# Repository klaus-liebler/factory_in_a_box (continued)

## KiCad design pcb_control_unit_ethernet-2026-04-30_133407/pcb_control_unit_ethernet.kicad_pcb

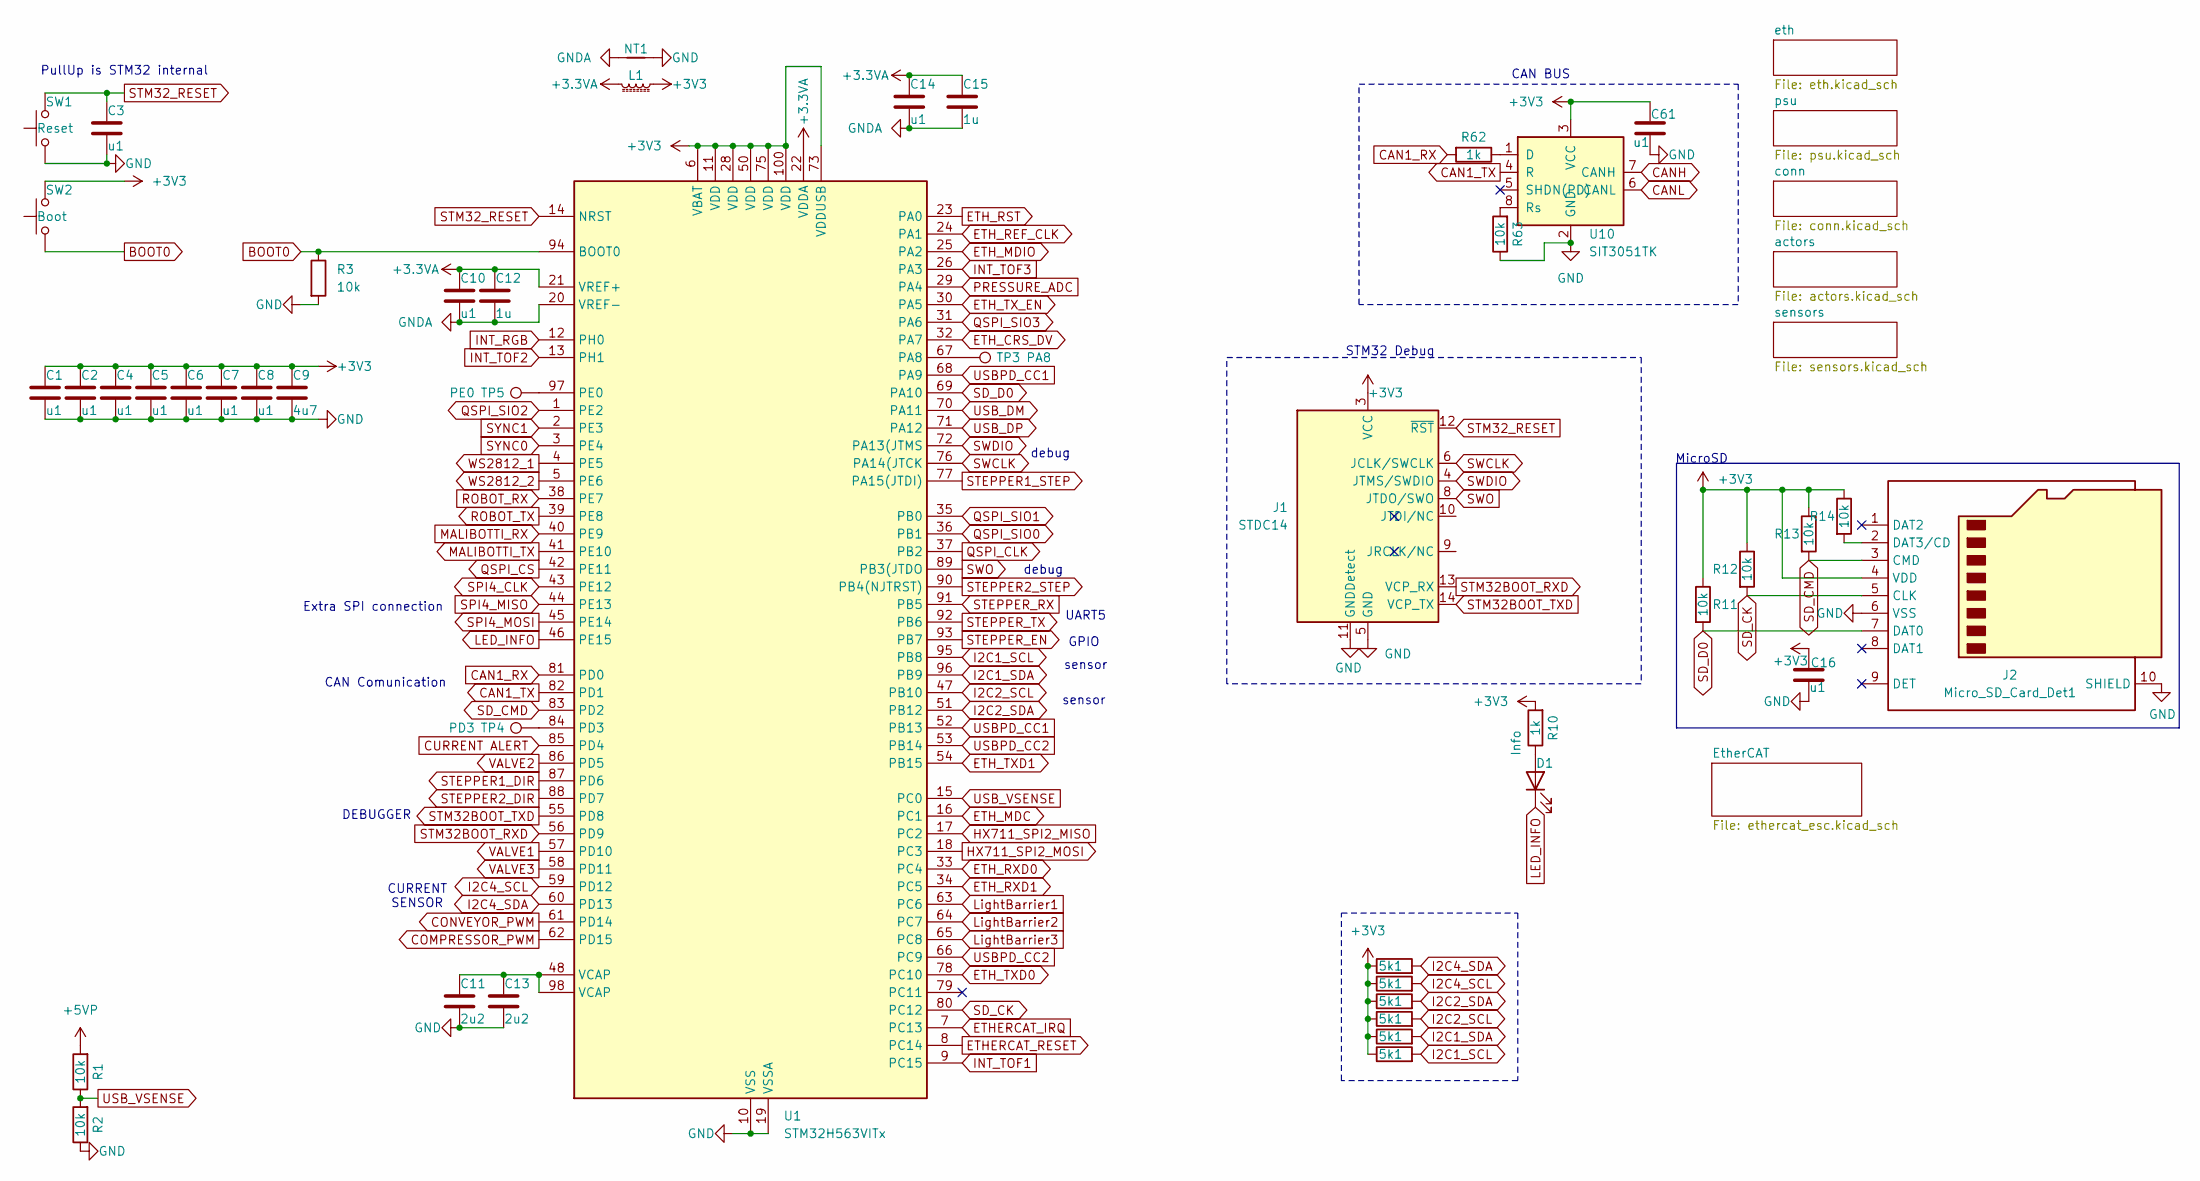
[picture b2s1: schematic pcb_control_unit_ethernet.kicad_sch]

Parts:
C1, C2, C3, C4, C5, C6, C7, C8, C10, C14: u1; C_0402_1005Metric
C9: 4u7; C_0402_1005Metric
C11, C13: 2u2; C_0402_1005Metric
C12, C15: 1u; C_0402_1005Metric
C16, C61: u1; C_0402_1005Metric; MPN GRM033R61A104KE15D
D1: Info; LED_1206_3216Metric_ReverseMount; MPN LTST-C230KRKT
J1: STDC14; IDC-Header_2x07_P1.27mm_Vertical_SMD
J2: Micro_SD_Card_Det1; microSD push; MPN TF PUSH
L1: 220R@100M; L_0603_1608Metric
NT1: NetTie_2; NetTie-2_SMD_Pad0.5mm
R1, R2, R11, R12, R13, R14, R63: 10k; R_0402_1005Metric; MPN 0201WMF1002TEE
R3: 10k; R_0402_1005Metric
R4, R5, R6, R7, R8, R9: 5k1; R_0402_1005Metric
R10, R62: 1k; R_0402_1005Metric; MPN 0402WGF1001TCE
SW1: Reset; SW_SPST_TL3342_smaller
SW2: Boot; SW_SPST_TL3342_smaller
TP3: PA8; TestPoint_THTPad_D1.0mm_Drill0.5mm
TP4: PD3; TestPoint_THTPad_D1.0mm_Drill0.5mm
TP5: PE0; TestPoint_THTPad_D1.0mm_Drill0.5mm
U1: STM32H563VITx; LQFP-100_14x14mm_P0.5mm
U10: SIT3051TK; DFN-8-1EP_3x3mm_P0.65mm_EP1.55x2.4mm

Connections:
+3.3VA: C10.1, C12.1, C14.1, C15.1, L1.2, U1.21 (VREF+), U1.22 (VDDA)
+3V3: C1.1, C2.1, C4.1, C5.1, C6.1, C7.1, C8.1, C9.1, C16.2, C61.1, J1.3 (VCC), J2.4 (VDD), L1.1, R4.1, R5.1, R6.1, R7.1, R8.1, R9.1, R10.2, R11.1, R12.1, R13.1, R14.1, SW2.2, U1.6 (VBAT), U1.11 (VDD), U1.28 (VDD), U1.50 (VDD), U1.73 (VDDUSB), U1.75 (VDD), U1.100 (VDD), U10.3 (VCC); also elsewhere on the board
+5VP: R1.2; also elsewhere on the board
BOOT0: R3.1, SW2.1, U1.94 (BOOT0)
CAN1_RX: R62.2, U1.81 (PD0)
CAN1_TX: U1.82 (PD1), U10.4 (R)
CANH: U10.7 (CANH); also elsewhere on the board
CANL: U10.6 (CANL); also elsewhere on the board
COMPRESSOR_PWM: U1.62 (PD15); also elsewhere on the board
CONVEYOR_PWM: U1.61 (PD14); also elsewhere on the board
CURRENT ALERT: U1.85 (PD4); also elsewhere on the board
ETHERCAT_IRQ: U1.7 (PC13); also elsewhere on the board
ETHERCAT_RESET: U1.8 (PC14); also elsewhere on the board
ETH_CRS_DV: U1.32 (PA7); also elsewhere on the board
ETH_MDC: U1.16 (PC1); also elsewhere on the board
ETH_MDIO: U1.25 (PA2); also elsewhere on the board
ETH_REF_CLK: U1.24 (PA1); also elsewhere on the board
ETH_RST: U1.23 (PA0); also elsewhere on the board
ETH_RXD0: U1.33 (PC4); also elsewhere on the board
ETH_RXD1: U1.34 (PC5); also elsewhere on the board
ETH_TXD0: U1.78 (PC10); also elsewhere on the board
ETH_TXD1: U1.54 (PB15); also elsewhere on the board
ETH_TX_EN: U1.30 (PA5); also elsewhere on the board
GND: C1.2, C2.2, C3.2, C4.2, C5.2, C6.2, C7.2, C8.2, C9.2, C11.2, C13.2, C16.1, C61.2, J1.5 (GND), J1.7 (GND), J1.11 (GNDDetect), J2.6 (VSS), J2.10 (SHIELD), NT1.2, R2.1, R3.2, R63.1, SW1.1, U1.10 (VSS), U1.19 (VSSA), U1.27 (VSS), U1.49 (VSS), U1.74 (VSS), U1.99 (VSS), U10.2 (GND), U10.9 (PAD); also elsewhere on the board
GNDA: C10.2, C12.2, C14.2, C15.2, NT1.1, U1.20 (VREF-)
HX711_SPI2_MISO: U1.17 (PC2); also elsewhere on the board
HX711_SPI2_MOSI: U1.18 (PC3); also elsewhere on the board
I2C1_SCL: R9.2, U1.95 (PB8); also elsewhere on the board
I2C1_SDA: R8.2, U1.96 (PB9); also elsewhere on the board
I2C2_SCL: R7.2, U1.47 (PB10); also elsewhere on the board
I2C2_SDA: R6.2, U1.51 (PB12); also elsewhere on the board
I2C4_SCL: R5.2, U1.59 (PD12); also elsewhere on the board
I2C4_SDA: R4.2, U1.60 (PD13); also elsewhere on the board
INT_RGB: U1.12 (PH0); also elsewhere on the board
INT_TOF1: U1.9 (PC15); also elsewhere on the board
INT_TOF2: U1.13 (PH1); also elsewhere on the board
INT_TOF3: U1.26 (PA3); also elsewhere on the board
LED_INFO: D1.1 (K), U1.46 (PE15)
LightBarrier1: U1.63 (PC6); also elsewhere on the board
LightBarrier2: U1.64 (PC7); also elsewhere on the board
LightBarrier3: U1.65 (PC8); also elsewhere on the board
MALIBOTTI_RX: U1.40 (PE9); also elsewhere on the board
MALIBOTTI_TX: U1.41 (PE10); also elsewhere on the board
unnamed: C11.1, C13.1, U1.48 (VCAP), U1.98 (VCAP)
unnamed: D1.2 (A), R10.1
unnamed: J2.2 (DAT3/CD), R14.2
unnamed: TP3.1 (1_1), U1.67 (PA8)
unnamed: TP4.1 (1_1), U1.84 (PD3)
unnamed: TP5.1 (1_1), U1.97 (PE0)
unnamed: R62.1, U10.1 (D)
unnamed: R63.2, U10.8 (Rs)
PRESSURE_ADC: U1.29 (PA4); also elsewhere on the board
QSPI_CLK: U1.37 (PB2); also elsewhere on the board
QSPI_CS: U1.42 (PE11); also elsewhere on the board
QSPI_SIO0: U1.36 (PB1); also elsewhere on the board
QSPI_SIO1: U1.35 (PB0); also elsewhere on the board
QSPI_SIO2: U1.1 (PE2); also elsewhere on the board
QSPI_SIO3: U1.31 (PA6); also elsewhere on the board
ROBOT_RX: U1.38 (PE7); also elsewhere on the board
ROBOT_TX: U1.39 (PE8); also elsewhere on the board
SD_CK: J2.5 (CLK), R12.2, U1.80 (PC12)
SD_CMD: J2.3 (CMD), R13.2, U1.83 (PD2)
SD_D0: J2.7 (DAT0), R11.2, U1.69 (PA10)
SPI4_CLK: U1.43 (PE12); also elsewhere on the board
SPI4_MISO: U1.44 (PE13); also elsewhere on the board
SPI4_MOSI: U1.45 (PE14); also elsewhere on the board
STEPPER1_DIR: U1.87 (PD6); also elsewhere on the board
STEPPER1_STEP: U1.77 (PA15(JTDI)); also elsewhere on the board
STEPPER2_DIR: U1.88 (PD7); also elsewhere on the board
STEPPER2_STEP: U1.90 (PB4(NJTRST)); also elsewhere on the board
STEPPER_EN: U1.93 (PB7); also elsewhere on the board
STEPPER_RX: U1.91 (PB5); also elsewhere on the board
STEPPER_TX: U1.92 (PB6); also elsewhere on the board
STM32BOOT_RXD: J1.13 (VCP_RX), U1.56 (PD9)
STM32BOOT_TXD: J1.14 (VCP_TX), U1.55 (PD8)
STM32_RESET: C3.1, J1.12 (~RST), SW1.2, U1.14 (NRST)
SWCLK: J1.6 (JCLK/SWCLK), U1.76 (PA14(JTCK)
SWDIO: J1.4 (JTMS/SWDIO), U1.72 (PA13(JTMS)
SWO: J1.8 (JTDO/SWO), U1.89 (PB3(JTDO)
SYNC0: U1.3 (PE4); also elsewhere on the board
SYNC1: U1.2 (PE3); also elsewhere on the board
USBPD_CC1: U1.52 (PB13), U1.68 (PA9); also elsewhere on the board
USBPD_CC2: U1.53 (PB14), U1.66 (PC9); also elsewhere on the board
USB_DM: U1.70 (PA11); also elsewhere on the board
USB_DP: U1.71 (PA12); also elsewhere on the board
USB_VSENSE: R1.1, R2.2, U1.15 (PC0)
VALVE1: U1.57 (PD10); also elsewhere on the board
VALVE2: U1.86 (PD5); also elsewhere on the board
VALVE3: U1.58 (PD11); also elsewhere on the board
WS2812_1: U1.4 (PE5); also elsewhere on the board
WS2812_2: U1.5 (PE6); also elsewhere on the board

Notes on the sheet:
CAN Comunication
debug
MicroSD
UART5
CAN BUS
DEBUGGER
sensor
STM32 Debug
CURRENT SENSOR
PullUp is STM32 internal
Extra SPI connection
GPIO

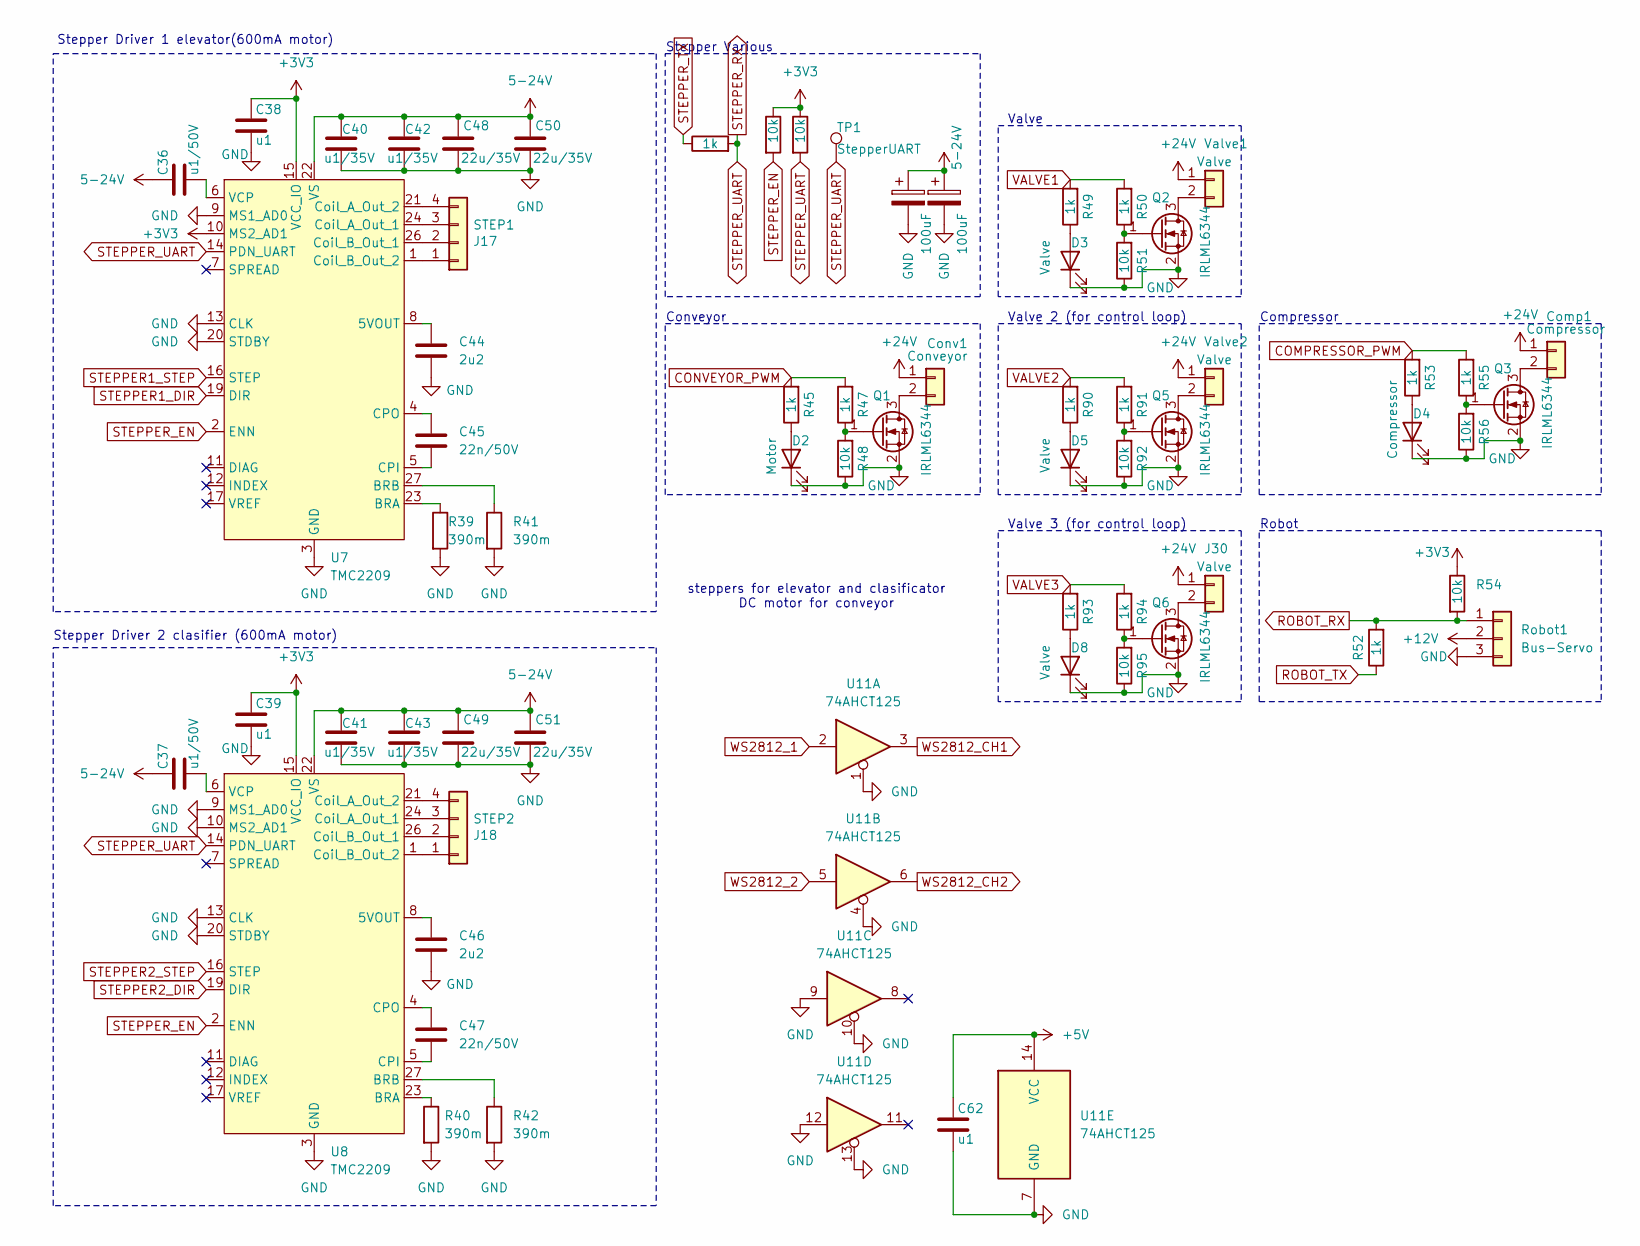
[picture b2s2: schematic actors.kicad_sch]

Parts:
C36, C37: u1/50V; C_0805_2012Metric; MPN GRM033R61A104KE15D
C38, C39, C62: u1; C_0402_1005Metric; MPN GRM033R61A104KE15D
C40, C41, C42, C43: u1/35V; C_0805_2012Metric; MPN CC0603KRX7R9BB104
C44, C46: 2u2; C_0402_1005Metric; MPN CL05A225MQ5NSNC
C45, C47: 22n/50V; C_0402_1005Metric; MPN GRM155R71H223KA12D
C48, C49, C50, C51: 22u/35V; C_0805_2012Metric; MPN CGA0805X5R226M350MT
C52, C53: 100uF; CP_Elec_6.3x7.7
Comp1: Compressor; PhoenixContact_MC_1,5_2-G-3.5_1x02_P3.50mm_Horizontal_small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
Conv1: Conveyor; PhoenixContact_MC_1,5_2-G-3.5_1x02_P3.50mm_Horizontal_small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
D2: Motor; LED_1206_3216Metric_ReverseMount; MPN LTST-C230KRKT
D3, D5, D8: Valve; LED_1206_3216Metric_ReverseMount; MPN LTST-C230KRKT
D4: Compressor; LED_1206_3216Metric_ReverseMount; MPN LTST-C230KRKT
J17: STEP1; JST_XH_B4B-XH-A_1x04_P2.50mm_Vertical_smaller; MPN XH-4AW
J18: STEP2; JST_XH_B4B-XH-A_1x04_P2.50mm_Vertical_smaller; MPN XH-4AW
J30: Valve; PhoenixContact_MC_1,5_2-G-3.5_1x02_P3.50mm_Horizontal_small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
Q1, Q2, Q3, Q5, Q6: IRLML6344; SOT-23; MPN AO3400
R39, R40, R41, R42: 390m; R_1206_3216Metric; MPN FRM121WFR100TM
R43, R52: 1k; R_0402_1005Metric
R44, R46, R54: 10k; R_0402_1005Metric
R45, R47, R49, R50, R53, R55, R90, R91, R93, R94: 1k; R_0402_1005Metric; MPN 0402WGF1001TCE
R48, R51, R56, R92, R95: 10k; R_0402_1005Metric; MPN 0201WMF1002TEE
Robot1: Bus-Servo; Molex_SPOX_5267-03A_1x03_P2.50mm_Vertical; MPN 5267-03A / 22035035
TP1: StepperUART; TestPoint_THTPad_D1.0mm_Drill0.5mm
U7, U8: TMC2209; QFN-28-1EP_5x5mm_P0.5mm_EP3.75x3.75mm_ThermalVias; MPN TMC2209-LA-T
U11: 74AHCT125; SOIC-14_3.9x8.7mm_P1.27mm
Valve1, Valve2: Valve; PhoenixContact_MC_1,5_2-G-3.5_1x02_P3.50mm_Horizontal_small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

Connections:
5-24V: C36.1, C37.1, C40.1, C41.1, C42.1, C43.1, C48.2, C49.2, C50.2, C51.2, C52.1, C53.1, U7.22 (VS), U7.28 (VS), U8.22 (VS), U8.28 (VS); also elsewhere on the board
+3V3: C38.1, C39.1, R44.1, R46.1, R54.1, U7.10 (MS2_AD1), U7.15 (VCC_IO), U8.15 (VCC_IO); also elsewhere on the board
+5V: C62.1, U11.14 (VCC); also elsewhere on the board
+12V: Robot1.2; also elsewhere on the board
+24V: Comp1.1, Conv1.1, J30.1, Valve1.1, Valve2.1; also elsewhere on the board
COMPRESSOR_PWM: R53.2, R55.2; also elsewhere on the board
CONVEYOR_PWM: R45.2, R47.2; also elsewhere on the board
GND: C38.2, C39.2, C40.2, C41.2, C42.2, C43.2, C44.2, C46.2, C48.1, C49.1, C50.1, C51.1, C52.2, C53.2, C62.2, D2.1 (K), D3.1 (K), D4.1 (K), D5.1 (K), D8.1 (K), Q1.2 (S), Q2.2 (S), Q3.2 (S), Q5.2 (S), Q6.2 (S), R39.2, R40.2, R41.2, R42.2, R48.1, R51.1, R56.1, R92.1, R95.1, Robot1.3, U7.3 (GND), U7.9 (MS1_AD0), U7.13 (CLK), U7.18 (GND), U7.20 (STDBY), U7.25 (GND), U7.29 (PAD), U8.3 (GND), U8.9 (MS1_AD0), U8.10 (MS2_AD1), U8.13 (CLK), U8.18 (GND), U8.20 (STDBY), U8.25 (GND), U8.29 (PAD), U11.1, U11.4, U11.7 (GND), U11.9, U11.10, U11.12, U11.13; also elsewhere on the board
unnamed: Comp1.2, Q3.3 (D)
unnamed: Conv1.2, Q1.3 (D)
unnamed: D2.2 (A), R45.1
unnamed: D3.2 (A), R49.1
unnamed: D4.2 (A), R53.1
unnamed: D5.2 (A), R90.1
unnamed: D8.2 (A), R93.1
unnamed: J17.1, U7.1 (Coil_B_Out_2)
unnamed: J17.2, U7.26 (Coil_B_Out_1)
unnamed: J17.3, U7.24 (Coil_A_Out_1)
unnamed: J17.4, U7.21 (Coil_A_Out_2)
unnamed: J18.1, U8.1 (Coil_B_Out_2)
unnamed: J18.2, U8.26 (Coil_B_Out_1)
unnamed: J18.3, U8.24 (Coil_A_Out_1)
unnamed: J18.4, U8.21 (Coil_A_Out_2)
unnamed: J30.2, Q6.3 (D)
unnamed: Q1.1 (G), R47.1, R48.2
unnamed: Q2.3 (D), Valve1.2
unnamed: Q2.1 (G), R50.1, R51.2
unnamed: Q3.1 (G), R55.1, R56.2
unnamed: Q5.3 (D), Valve2.2
unnamed: Q5.1 (G), R91.1, R92.2
unnamed: Q6.1 (G), R94.1, R95.2
unnamed: C44.1, U7.8 (5VOUT)
unnamed: R39.1, U7.23 (BRA)
unnamed: R41.1, U7.27 (BRB)
unnamed: C45.2, U7.5 (CPI)
unnamed: C45.1, U7.4 (CPO)
unnamed: C36.2, U7.6 (VCP)
unnamed: C46.1, U8.8 (5VOUT)
unnamed: R40.1, U8.23 (BRA)
unnamed: R42.1, U8.27 (BRB)
unnamed: C47.2, U8.5 (CPI)
unnamed: C47.1, U8.4 (CPO)
unnamed: C37.2, U8.6 (VCP)
ROBOT_RX: R52.2, R54.2, Robot1.1; also elsewhere on the board
ROBOT_TX: R52.1; also elsewhere on the board
STEPPER1_DIR: U7.19 (DIR); also elsewhere on the board
STEPPER1_STEP: U7.16 (STEP); also elsewhere on the board
STEPPER2_DIR: U8.19 (DIR); also elsewhere on the board
STEPPER2_STEP: U8.16 (STEP); also elsewhere on the board
STEPPER_EN: R44.2, U7.2 (ENN), U8.2 (ENN); also elsewhere on the board
STEPPER_RX: R43.2, R46.2, TP1.1 (1_1), U7.14 (PDN_UART), U8.14 (PDN_UART); also elsewhere on the board
STEPPER_TX: R43.1; also elsewhere on the board
VALVE1: R49.2, R50.2; also elsewhere on the board
VALVE2: R90.2, R91.2; also elsewhere on the board
VALVE3: R93.2, R94.2; also elsewhere on the board
WS2812_1: U11.2; also elsewhere on the board
WS2812_2: U11.5; also elsewhere on the board
WS2812_CH1: U11.3; also elsewhere on the board
WS2812_CH2: U11.6; also elsewhere on the board

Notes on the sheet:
Robot
Valve 2 (for control loop)
Compressor
Stepper Driver 2 clasifier (600mA motor)
steppers for elevator and clasificator DC motor for conveyor
Valve 3 (for control loop)
Stepper Driver 1 elevator(600mA motor)
Conveyor
Stepper Various
Valve

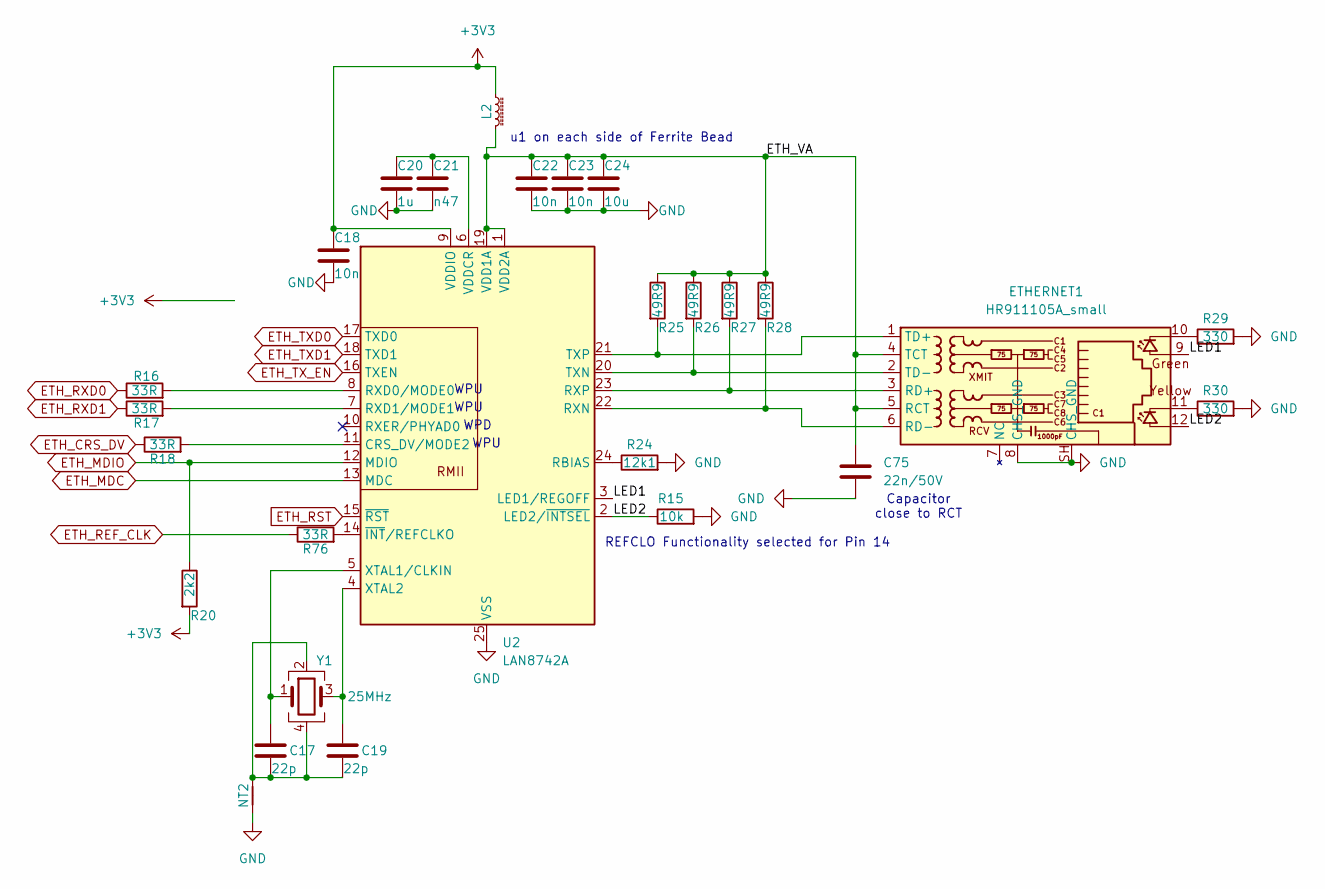
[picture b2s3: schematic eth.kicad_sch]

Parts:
C17, C19: 22p; C_0402_1005Metric
C18, C22, C23: 10n; C_0402_1005Metric
C20: 1u; C_0402_1005Metric
C21: n47; C_0402_1005Metric
C24: 10u; C_0603_1608Metric
C75: 22n/50V; C_0402_1005Metric; MPN GRM155R71H223KA12D
ETHERNET1: HR911105A_small; RJ45_HANRUN_HR911105A
L2: 600R@100M; L_0603_1608Metric
NT2: NetTie_2; NetTie-2_SMD_Pad0.5mm
R15: 10k; R_0402_1005Metric
R16, R17, R18, R76: 33R; R_0402_1005Metric
R20: 2k2; R_0402_1005Metric
R24: 12k1; R_0402_1005Metric
R25, R26, R27, R28: 49R9; R_0402_1005Metric
R29, R30: 330; R_0402_1005Metric
U2: LAN8742A; VQFN-24-1EP_4x4mm_P0.5mm_EP2.5x2.5mm_ThermalVias
Y1: 25MHz; Crystal_SMD_2016-4Pin_2.0x1.6mm

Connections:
+3V3: C18.1, L2.1, R20.2, U2.9 (VDDIO); also elsewhere on the board
/eth/ETH_VA: C22.1, C23.1, C24.1, C75.1, ETHERNET1.4 (TCT), ETHERNET1.5 (RCT), L2.2, R25.1, R26.1, R27.1, R28.1, U2.1 (VDD2A), U2.19 (VDD1A)
/eth/LED1: ETHERNET1.9, U2.3 (LED1/REGOFF)
/eth/LED2: ETHERNET1.12, R15.1, U2.2 (LED2/~INTSEL)
ETH_CRS_DV: R18.1; also elsewhere on the board
ETH_MDC: U2.13 (MDC); also elsewhere on the board
ETH_MDIO: R20.1, U2.12 (MDIO); also elsewhere on the board
ETH_REF_CLK: R76.1; also elsewhere on the board
ETH_RST: U2.15 (~RST); also elsewhere on the board
ETH_RXD0: R16.1; also elsewhere on the board
ETH_RXD1: R17.1; also elsewhere on the board
ETH_TXD0: U2.17 (TXD0); also elsewhere on the board
ETH_TXD1: U2.18 (TXD1); also elsewhere on the board
ETH_TX_EN: U2.16 (TXEN); also elsewhere on the board
GND: C18.2, C20.2, C21.2, C22.2, C23.2, C24.2, C75.2, ETHERNET1.8 (CHS_GND), ETHERNET1.SH (CHS_GND), NT2.1, R15.2, R24.2, R29.2, R30.2, U2.25 (VSS); also elsewhere on the board
unnamed: C17.2, C19.2, NT2.2, Y1.2, Y1.4
unnamed: ETHERNET1.10, R29.1
unnamed: ETHERNET1.11, R30.1
unnamed: ETHERNET1.3 (RD+), R27.2, U2.23 (RXP)
unnamed: ETHERNET1.6 (RD-), R28.2, U2.22 (RXN)
unnamed: ETHERNET1.1 (TD+), R25.2, U2.21 (TXP)
unnamed: ETHERNET1.2 (TD-), R26.2, U2.20 (TXN)
unnamed: R18.2, U2.11 (CRS_DV/MODE2)
unnamed: R24.1, U2.24 (RBIAS)
unnamed: R16.2, U2.8 (RXD0/MODE0)
unnamed: R17.2, U2.7 (RXD1/MODE1)
unnamed: C20.1, C21.1, U2.6 (VDDCR)
unnamed: C17.1, U2.5 (XTAL1/CLKIN), Y1.1
unnamed: C19.1, U2.4 (XTAL2), Y1.3
unnamed: R76.2, U2.14 (~INT/REFCLKO)

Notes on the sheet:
Capacitor close to RCT
u1 on each side of Ferrite Bead
WPU
REFCLO Functionality selected for Pin 14
WPD

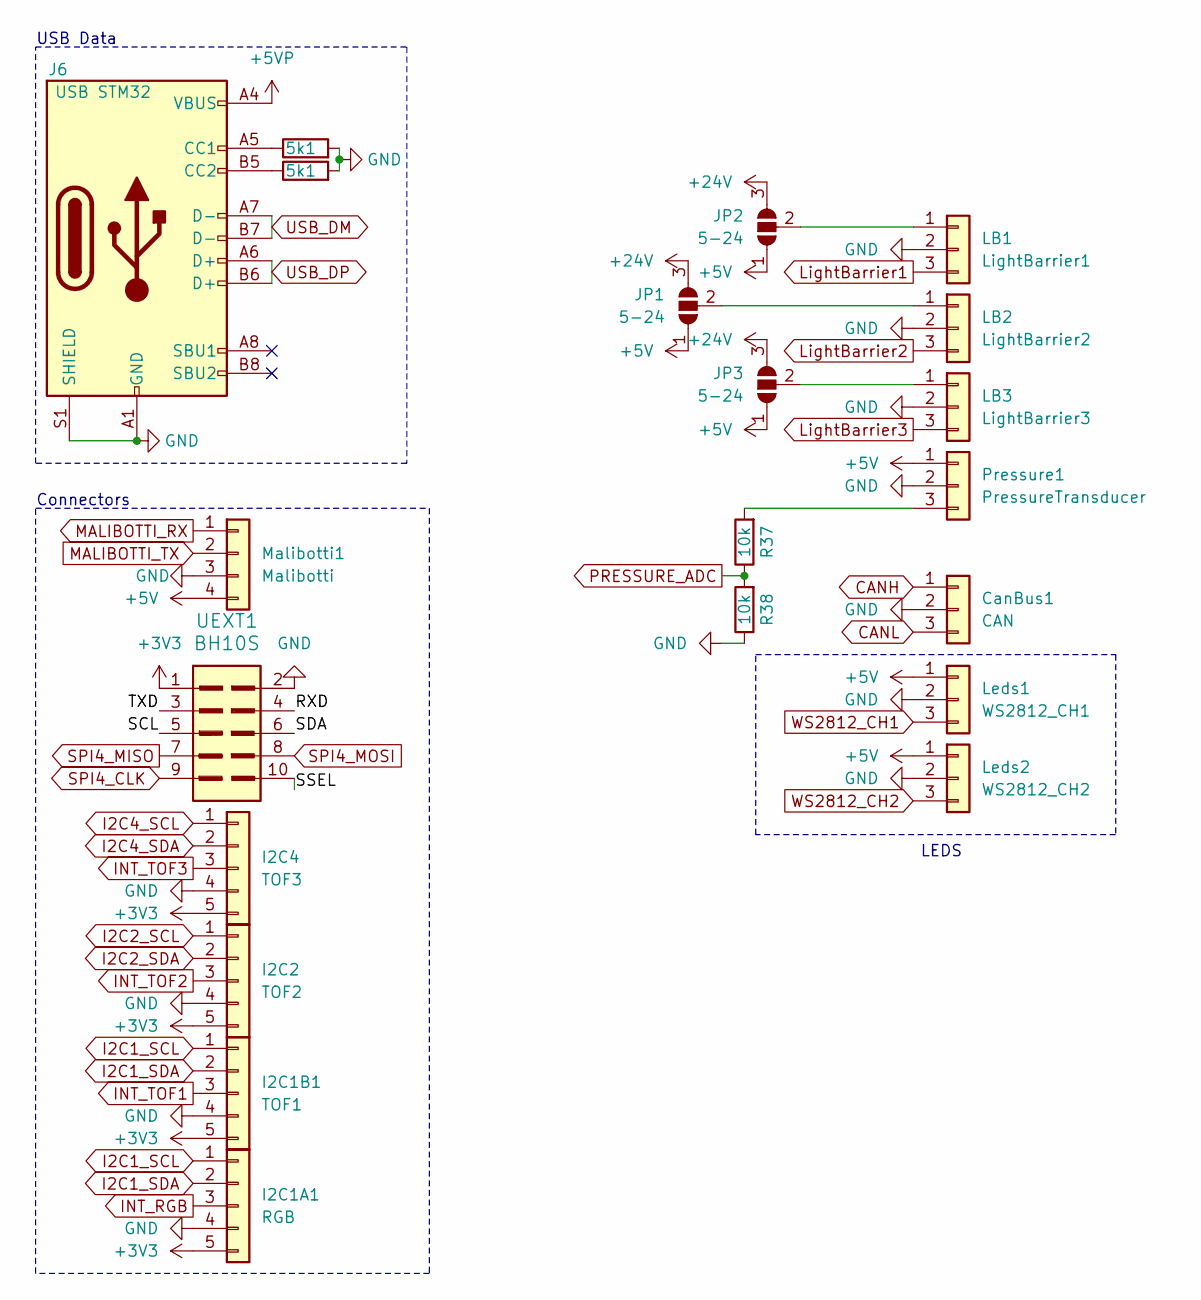
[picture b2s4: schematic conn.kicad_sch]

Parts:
CanBus1: CAN; JST_XH_B3B-XH-A_1x03_P2.50mm_Vertical_smaller
I2C1A1: RGB; JST_XH_B5B-XH-A_1x05_P2.50mm_Vertical_smaller
I2C1B1: TOF1; JST_XH_B5B-XH-A_1x05_P2.50mm_Vertical_smaller
I2C2: TOF2; JST_XH_B5B-XH-A_1x05_P2.50mm_Vertical_smaller
I2C4: TOF3; JST_XH_B5B-XH-A_1x05_P2.50mm_Vertical_smaller
J6: USB STM32; USB_C_Receptacle_HRO_TYPE-C-31-M-12_smaller; MPN TYPE-C-31-M-12
JP1, JP2, JP3: 5-24; SolderJumper-3_P1.3mm_Open_RoundedPad1.0x1.5mm_NumberLabels
LB1: LightBarrier1; JST_XH_B3B-XH-A_1x03_P2.50mm_Vertical_smaller
LB2: LightBarrier2; JST_XH_B3B-XH-A_1x03_P2.50mm_Vertical_smaller
LB3: LightBarrier3; JST_XH_B3B-XH-A_1x03_P2.50mm_Vertical_smaller
Leds1: WS2812_CH1; JST_XH_B3B-XH-A_1x03_P2.50mm_Vertical_smaller
Leds2: WS2812_CH2; JST_XH_B3B-XH-A_1x03_P2.50mm_Vertical_smaller
Malibotti1: Malibotti; JST_XH_B4B-XH-A_1x04_P2.50mm_Vertical_smaller
Pressure1: PressureTransducer; JST_XH_B3B-XH-A_1x03_P2.50mm_Vertical_smaller
R35, R36: 5k1; R_0402_1005Metric
R37, R38: 10k; R_0402_1005Metric; MPN 0201WMF1002TEE
UEXT1: BH10S; UEXTM-PTH

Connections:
+3V3: I2C1A1.5, I2C1B1.5, I2C2.5, I2C4.5, UEXT1.1; also elsewhere on the board
+5V: JP1.1 (A), JP2.1 (A), JP3.1 (A), Leds1.1, Leds2.1, Malibotti1.4, Pressure1.1; also elsewhere on the board
+5VP: J6.A4 (VBUS), J6.A9 (VBUS), J6.B4 (VBUS), J6.B9 (VBUS); also elsewhere on the board
+24V: JP1.3 (B), JP2.3 (B), JP3.3 (B); also elsewhere on the board
/conn/RXD: UEXT1.4
/conn/SCL: UEXT1.5
/conn/SDA: UEXT1.6
/conn/SSEL: UEXT1.10
/conn/TXD: UEXT1.3
CANH: CanBus1.1; also elsewhere on the board
CANL: CanBus1.3; also elsewhere on the board
GND: CanBus1.2, I2C1A1.4, I2C1B1.4, I2C2.4, I2C4.4, J6.A1 (GND), J6.A12 (GND), J6.B1 (GND), J6.B12 (GND), J6.S1 (SHIELD), LB1.2, LB2.2, LB3.2, Leds1.2, Leds2.2, Malibotti1.3, Pressure1.2, R35.2, R36.2, R38.1, UEXT1.2; also elsewhere on the board
I2C1_SCL: I2C1A1.1, I2C1B1.1; also elsewhere on the board
I2C1_SDA: I2C1A1.2, I2C1B1.2; also elsewhere on the board
I2C2_SCL: I2C2.1; also elsewhere on the board
I2C2_SDA: I2C2.2; also elsewhere on the board
I2C4_SCL: I2C4.1; also elsewhere on the board
I2C4_SDA: I2C4.2; also elsewhere on the board
INT_RGB: I2C1A1.3; also elsewhere on the board
INT_TOF1: I2C1B1.3; also elsewhere on the board
INT_TOF2: I2C2.3; also elsewhere on the board
INT_TOF3: I2C4.3; also elsewhere on the board
LightBarrier1: LB1.3; also elsewhere on the board
LightBarrier2: LB2.3; also elsewhere on the board
LightBarrier3: LB3.3; also elsewhere on the board
MALIBOTTI_RX: Malibotti1.1; also elsewhere on the board
MALIBOTTI_TX: Malibotti1.2; also elsewhere on the board
unnamed: J6.A5 (CC1), R35.1
unnamed: J6.B5 (CC2), R36.1
unnamed: JP1.2 (C), LB2.1
unnamed: JP2.2 (C), LB1.1
unnamed: JP3.2 (C), LB3.1
unnamed: Pressure1.3, R37.2
PRESSURE_ADC: R37.1, R38.2; also elsewhere on the board
SPI4_CLK: UEXT1.9; also elsewhere on the board
SPI4_MISO: UEXT1.7; also elsewhere on the board
SPI4_MOSI: UEXT1.8; also elsewhere on the board
USB_DM: J6.A7 (D-), J6.B7 (D-); also elsewhere on the board
USB_DP: J6.A6 (D+), J6.B6 (D+); also elsewhere on the board
WS2812_CH1: Leds1.3; also elsewhere on the board
WS2812_CH2: Leds2.3; also elsewhere on the board

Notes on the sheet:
Connectors
LEDS
USB Data

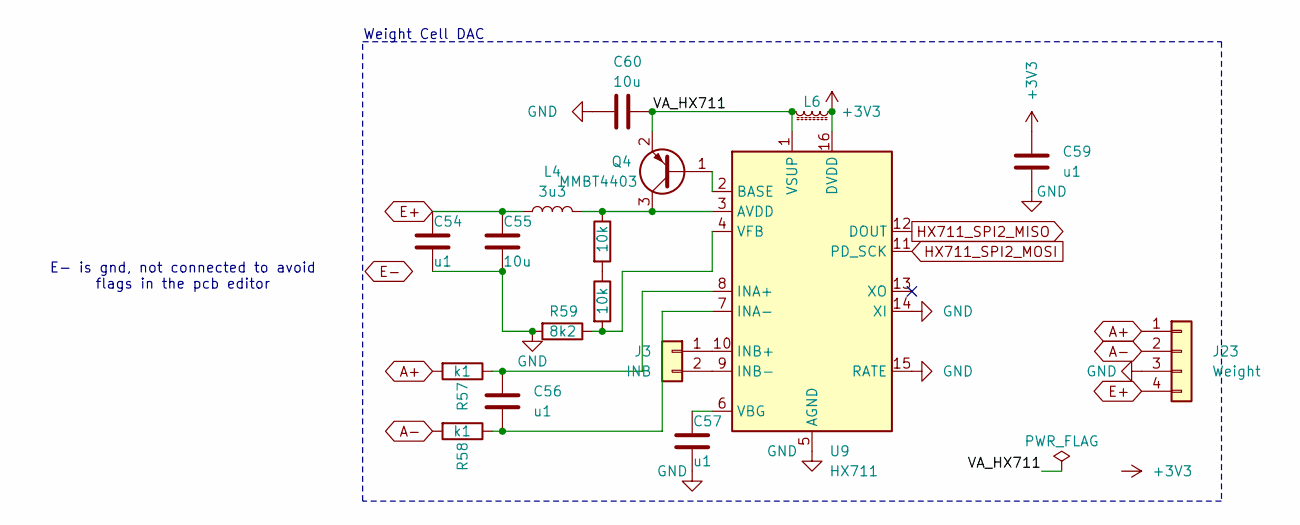
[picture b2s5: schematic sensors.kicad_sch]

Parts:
C54, C56, C57, C59: u1; C_0402_1005Metric
C55, C60: 10u; C_0805_2012Metric
J3: INB; JST_XH_B2B-XH-A_1x02_P2.50mm_Vertical
J23: Weight; JST_XH_B4B-XH-A_1x04_P2.50mm_Vertical_smaller
L4: 3u3; L_0805_2012Metric
L6: 220R@100M; L_0603_1608Metric
Q4: MMBT4403; SOT-23_smaller
R57, R58: k1; R_0402_1005Metric
R59: 8k2; R_0402_1005Metric
R60, R61: 10k; R_0402_1005Metric
U9: HX711; SOIC-16_3.9x9.9mm_P1.27mm

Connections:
+3V3: C59.1, L6.1, U9.16 (DVDD); also elsewhere on the board
/sensors/VA_HX711: C60.1, L6.2, Q4.2 (E), U9.1 (VSUP)
A+: J23.1, R57.2
A-: J23.2, R58.2
E+: C54.1, C55.1, J23.4, L4.1
GND: C54.2, C55.2, C57.2, C59.2, C60.2, J23.3, R59.2, U9.5 (AGND), U9.14 (XI), U9.15 (RATE); also elsewhere on the board
HX711_SPI2_MISO: U9.12 (DOUT); also elsewhere on the board
HX711_SPI2_MOSI: U9.11 (PD_SCK); also elsewhere on the board
unnamed: J3.1, U9.10 (INB+)
unnamed: J3.2, U9.9 (INB-)
unnamed: Q4.1 (B), U9.2 (BASE)
unnamed: L4.2, Q4.3 (C), R60.1, U9.3 (AVDD)
unnamed: R60.2, R61.1
unnamed: C56.1, R57.1, U9.8 (INA+)
unnamed: C56.2, R58.1, U9.7 (INA-)
unnamed: C57.1, U9.6 (VBG)
unnamed: R59.1, R61.2, U9.4 (VFB)

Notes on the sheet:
Weight Cell DAC
E- is gnd, not connected to avoid flags in the pcb editor

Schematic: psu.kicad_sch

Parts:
C27, C76: u1/35V; C_0805_2012Metric; MPN CC0603KRX7R9BB104
C28, C80: 10u/35V; C_0805_2012Metric; MPN CGA0805X5R106K350MT
C29, C84: u1/16V; C_0402_1005Metric; MPN CC0603KRX7R9BB104
C30, C88: 56p; C_0402_1005Metric; MPN CC0402JRNPO9BN560
C31, C32, C34, C89, C98: 22u; C_0805_2012Metric; MPN CL10A226MP8NUNE
C33: 10u; C_0805_2012Metric
C35: u1; C_0402_1005Metric; MPN GRM033R61A104KE15D
J4: DC IN; BarrelJack_Horizontal; MPN DC-005 2.0
J5: USB STM32; USB_C_Receptacle_HRO_TYPE-C-31-M-12_smaller; MPN TYPE-C-31-M-12
L3, L10: 12uH; L_Abracon_ASPI-0630LR; MPN FXL0630-100-M
R31: 3k3; R_0402_1005Metric; MPN 0402WGF3301TCE
R32, R88: M1; R_0402_1005Metric; MPN 0201WMF1003TEE
R33: 10k; R_0402_1005Metric; MPN 0201WMF1002TEE
R34: 2m; R_1206_3216Metric
R87: 5k1; R_0402_1005Metric
R89: 10k; R_0402_1005Metric
R96: 330; R_0402_1005Metric
U4, U12: TPS54202DDC; SOT-23-6_Handsoldering; MPN TPS54202DDCR
U5: AMS1117-3.3; SOT-223-3_TabPin2
U6: INA226; TSSOP-10_3x3mm_P0.5mm
X1: MT3608; DCDC_MT3608

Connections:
5-24V: C27.2, C28.2, C76.2, C80.2, R34.2, U4.3 (VIN), U6.9 (Vin-), U12.3 (VIN), X1.1 (In+); also elsewhere on the board
+3V3: C34.1, C35.1, R89.1, U5.2 (VO), U6.6 (VS); also elsewhere on the board
+5V: C30.2, C31.1, C32.1, C33.1, L3.1, R32.1, U5.3 (VI); also elsewhere on the board
+12V: C88.2, C89.1, C98.1, L10.1, R88.1; also elsewhere on the board
+24V: X1.4 (out+); also elsewhere on the board
+VDC: J4.1, J5.A4 (VBUS), J5.A9 (VBUS), J5.B4 (VBUS), J5.B9 (VBUS), R34.1, U6.8 (Vbus), U6.10 (Vin+)
/psu/BOOT: C29.1, U4.6 (BOOT)
/psu/BOOT12: C84.1, U12.6 (BOOT)
/psu/FB: C30.1, R32.2, R33.2, U4.4 (FB)
/psu/FB12: C88.1, R88.2, R96.2, U12.4 (FB)
/psu/SW: C29.2, L3.2, U4.2 (SW)
/psu/SW12: C84.2, L10.2, U12.2 (SW)
CURRENT ALERT: R89.2, U6.3 (~Alert); also elsewhere on the board
GND: C27.1, C28.1, C31.2, C32.2, C33.2, C34.2, C35.2, C76.1, C80.1, C89.2, C98.2, J4.2, J4.3, J5.A1 (GND), J5.A12 (GND), J5.B1 (GND), J5.B12 (GND), J5.S1 (SHIELD), R31.1, R87.1, U4.1 (GND), U5.1 (GND), U6.1 (A1), U6.2 (A0), U6.7 (GND), U12.1 (GND), X1.2 (In-), X1.3 (out-); also elsewhere on the board
I2C4_SCL: U6.5 (SCL); also elsewhere on the board
I2C4_SDA: U6.4 (SDA); also elsewhere on the board
unnamed: R31.2, R33.1
unnamed: R87.2, R96.1
USBPD_CC1: J5.B5 (CC2); also elsewhere on the board
USBPD_CC2: J5.A5 (CC1); also elsewhere on the board

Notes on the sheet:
PSU 5V
Barrel Jack 24V
Power sensor
PSU 12V
USB PD
5V - 3.3V
24V - 5-24V
